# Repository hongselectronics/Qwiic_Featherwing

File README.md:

# Qwiic_Featherwing
An Adafruit Featherwing (Feather expansion board) protoboard with Sparkfun Qwiic connectors

Original Feather Feather Protowing:
Designed by Adafruit Industries.
Creative Commons Attribution, Share-Alike license, check license.txt for more information All text above must be included in any redistribution

The Qwiic system: [Sparkfun: What is Qwiic?](https://www.sparkfun.com/qwiic)

<a href="https://oshpark.com/shared_projects/GCelqpc8"></img></a>

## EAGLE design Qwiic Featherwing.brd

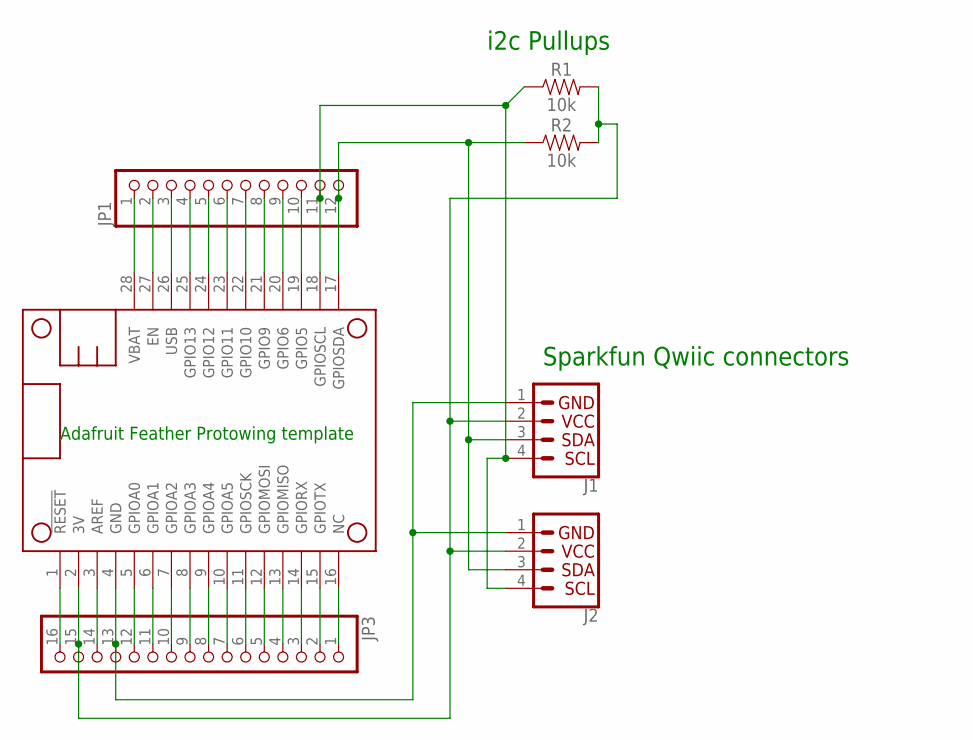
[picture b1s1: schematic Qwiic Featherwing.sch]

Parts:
J1, J2: QWIIC_CONNECTORJS-1MM; 1X04_1MM_RA
JP1: HEADER-1X1276MIL; 1X12_ROUND_76MIL
JP3: HEADER-1X16_76MIL; 1X16_ROUND_76MIL
MS1: FEATHERWING
R1, R2: 10k; 0603

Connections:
3V: J1.2 (VCC), J2.2 (VCC), JP3.15, MS1.2 (3V), R1.2, R2.2
AREF: JP3.14, MS1.3 (AREF)
GND: J1.1 (GND), J2.1 (GND), JP3.13, MS1.4 (GND)
unnamed: JP1.2, MS1.27 (EN)
unnamed: JP3.1, MS1.16 (NC)
unnamed: JP1.4, MS1.25 (GPIO13)
unnamed: JP3.2, MS1.15 (GPIOTX)
unnamed: JP1.5, MS1.24 (GPIO12)
unnamed: JP3.3, MS1.14 (GPIORX)
unnamed: JP3.4, MS1.13 (GPIOMISO)
unnamed: JP3.5, MS1.12 (GPIOMOSI)
unnamed: JP3.6, MS1.11 (GPIOSCK)
unnamed: JP3.7, MS1.10 (GPIOA5)
unnamed: JP3.8, MS1.9 (GPIOA4)
unnamed: JP3.9, MS1.8 (GPIOA3)
unnamed: JP3.10, MS1.7 (GPIOA2)
unnamed: JP3.11, MS1.6 (GPIOA1)
unnamed: JP3.12, MS1.5 (GPIOA0)
unnamed: JP3.16, MS1.1 (!RESET)
unnamed: JP1.6, MS1.23 (GPIO11)
unnamed: JP1.7, MS1.22 (GPIO10)
unnamed: JP1.8, MS1.21 (GPIO9)
unnamed: JP1.9, MS1.20 (GPIO6)
unnamed: JP1.10, MS1.19 (GPIO5)
unnamed: J1.4 (SCL), J2.4 (SCL), JP1.11, MS1.18 (GPIOSCL), R1.1
unnamed: J1.3 (SDA), J2.3 (SDA), JP1.12, MS1.17 (GPIOSDA), R2.1
USB: JP1.3, MS1.26 (USB)
VBAT: JP1.1, MS1.28 (VBAT)

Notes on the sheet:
Sparkfun Qwiic connectors
i2c Pullups
Adafruit Feather Protowing template

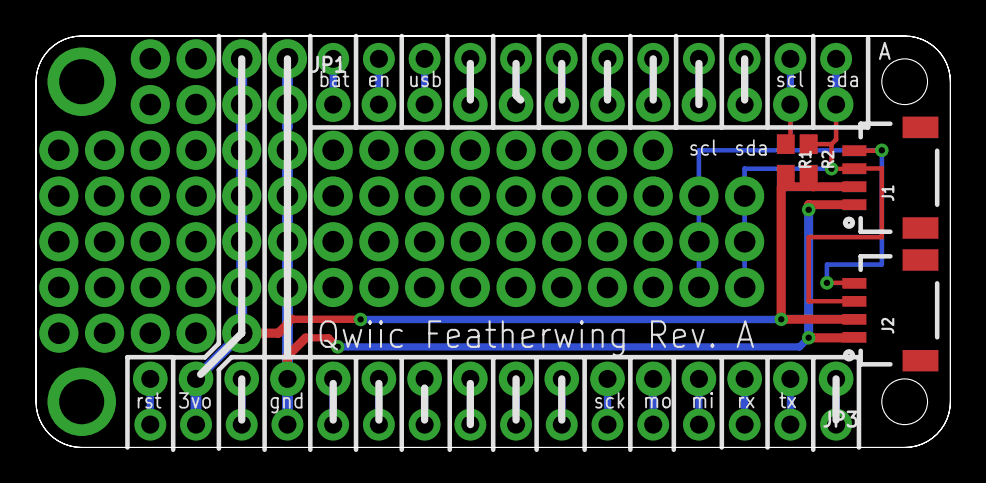
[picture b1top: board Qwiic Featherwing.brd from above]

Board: 2 copper layers, 50.8 x 22.9 mm, 7 parts (0 on the bottom side), 28 nets.

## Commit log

2018-02-08 Added brd and sch

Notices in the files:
parts and their libraries:
SparkFun-Connectors: Licensing: Creative Commons ShareAlike 4.0 International - https://creativecommons.org/licenses/by-sa/4.0
